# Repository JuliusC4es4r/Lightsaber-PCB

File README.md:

# Lightsaber-PCB
A lightsaber PCB for installing within lightsaber hilts. Designed to power and control neopixel LED strips and play sounds on a speaker. Charges its own battery via USB-C.

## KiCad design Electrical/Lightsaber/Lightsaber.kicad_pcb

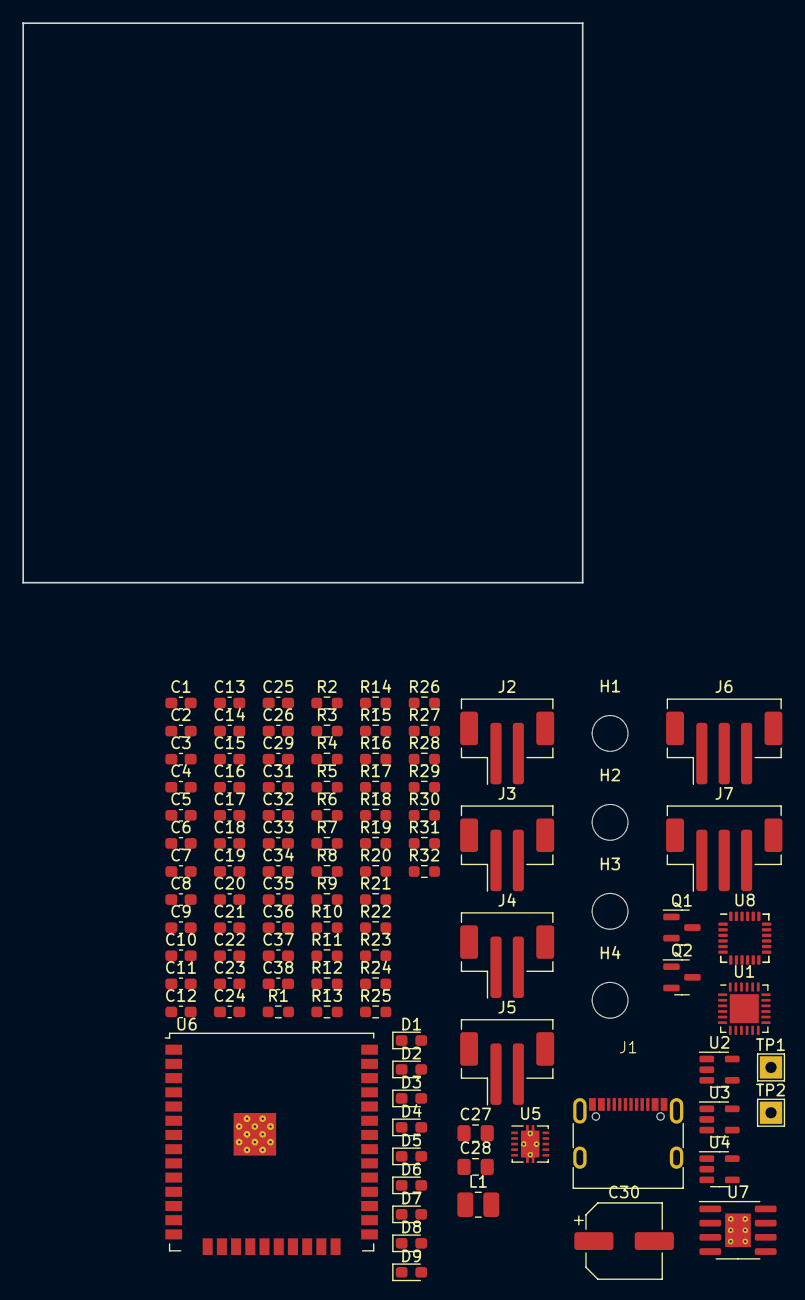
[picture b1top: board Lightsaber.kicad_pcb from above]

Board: 4 copper layers, 50.0 x 50.0 mm, 103 parts (0 on the bottom side), 58 nets, no tracks yet.

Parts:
C1, C3, C7, C8, C9, C12, C17, C32: 4u7; C_0603_1608Metric_Pad1.08x0.95mm_HandSolder
C2, C4, C10, C11, C16, C20, C29, C31, C33, C35, C37, C38: 100n; C_0603_1608Metric_Pad1.08x0.95mm_HandSolder
C5, C6, C13, C14, C15, C18, C19, C21, C22, C23, C24, C25, C26: 10uF; C_0603_1608Metric_Pad1.08x0.95mm_HandSolder
C27, C28: 10uF; C_0805_2012Metric_Pad1.18x1.45mm_HandSolder
C30: 100uF; CP_Elec_6.3x7.7
C34: 2.2n; C_0603_1608Metric_Pad1.08x0.95mm_HandSolder
C36: 10n; C_0603_1608Metric_Pad1.08x0.95mm_HandSolder
D1, D2, D4, D5: Blue; LED_0603_1608Metric_Pad1.05x0.95mm_HandSolder
D3, D6, D7, D8, D9: Green; LED_0603_1608Metric_Pad1.05x0.95mm_HandSolder
H1, H2, H3, H4: MountingHole; MountingHole_3.2mm_M3
J1: USB4105-GF-A; USB-C
J2, J3, J4, J5: B2B-PH-SM4-TB; JST_PH_B2B-PH-SM4-TB_1x02-1MP_P2.00mm_Vertical
J6, J7: B3B-PH-SM4-TB; JST_PH_B3B-PH-SM4-TB_1x03-1MP_P2.00mm_Vertical
L1: 2.2uH; L_1008_2520Metric_Pad1.43x2.20mm_HandSolder
Q1, Q2: BC817; SOT-23
R1, R11: 2kR; R_0603_1608Metric_Pad0.98x0.95mm_HandSolder
R2, R3: 5k1; R_0603_1608Metric_Pad0.98x0.95mm_HandSolder
R4, R5, R8, R9, R10, R12, R13, R16, R19, R25, R31, R32: 10kR; R_0603_1608Metric_Pad0.98x0.95mm_HandSolder
R6, R7, R21, R24, R26: 470R; R_0603_1608Metric_Pad0.98x0.95mm_HandSolder
R14: 100R; R_0603_1608Metric_Pad0.98x0.95mm_HandSolder
R15: 90.9kR; R_0603_1608Metric_Pad0.98x0.95mm_HandSolder
R17, R23: 0R; R_0603_1608Metric_Pad0.98x0.95mm_HandSolder
R18: 73.2kR; R_0603_1608Metric_Pad0.98x0.95mm_HandSolder
R20, R22, R28, R29, R30: 3.3k; R_0603_1608Metric_Pad0.98x0.95mm_HandSolder
R27: 10R; R_0603_1608Metric_Pad0.98x0.95mm_HandSolder
TP1, TP2: TestPoint; TestPoint_THTPad_2.0x2.0mm_Drill1.0mm
U1: CP2102N-Axx-xQFN24; QFN-24-1EP_4x4mm_P0.5mm_EP2.6x2.6mm
U2: MCP73831-2-OT; SOT-23-5
U3: AP2171W; SOT-23-5
U4: AP2161W; SOT-23-5
U5: TPS63000; Texas_DRC0010J_ThermalVias
U6: ESP32-WROOM-32U
U7: LM386; SOIC-8-1EP_3.9x4.9mm_P1.27mm_EP2.29x3mm_ThermalVias
U8: MPU-6050; InvenSense_QFN-24_4x4mm_P0.5mm

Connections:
+3V3: C3.1, C4.1, C17.1, C20.1, C21.1, C24.1, C33.1, C36.1, J3.1, J4.1, R1.1, R6.1, R7.1, R20.1, R22.1, R26.1, R31.1, R32.1, U1.5 (VIO), U1.6 (VDD), U6.2 (VDD), U8.8 (VLOGIC), U8.13 (VDD)
+5V: C7.1, C10.1, C13.1, C18.1, C19.1, C22.1, C23.1, C25.1, C26.1, C32.1, C35.1, J6.1, J7.1, R15.1, R30.1, U2.4 (V_{DD}), U3.1 (OUT), U5.1 (VOUT), U7.6 (V+)
+BATT: C5.1, C8.1, C12.1, J2.1, R11.1, U2.3 (V_{BAT}), U4.5 (IN)
/BOOT: C38.1, Q2.3 (C), R32.2, U6.25 (IO0)
/BTN_1: J3.2, R12.1, U6.26 (IO4)
/BTN_2: J4.2, R13.1, U6.29 (IO5)
/D+: J1.A6 (D+), J1.B6 (D+), U1.3 (D+)
/D-: J1.A7 (D-), J1.B7 (D-), U1.4 (D-)
/DAC: R17.1, R18.1, U6.10 (IO25)
/DOUT_1: J6.2, U6.27 (IO16)
/DOUT_2: J7.2, U6.28 (IO17)
/DTR: Q2.2 (E), R8.1, U1.23 (~DTR)
/EN: C37.1, Q1.3 (C), R31.2, U6.3 (EN)
/INT: U6.14 (IO12), U8.12 (INT)
/LED_1: R21.1, U6.30 (IO18)
/LED_2: R24.1, U6.31 (IO19)
/RST: R1.2, U1.9 (~RST)
/RTS: Q1.2 (E), R9.1, U1.19 (~RTS)
/RX: U1.20 (RXD), U6.35 (TXD0/IO1)
/SCL: R20.2, U6.36 (IO22), U8.23 (SCL)
/SDA: R22.2, U6.33 (IO21), U8.24 (SDA)
/SPKR_OUT: C30.2, J5.1
/TX: U1.21 (TXD), U6.34 (RXD0/IO3)
/VBUS_EN: R4.2, R5.1, U4.4 (~EN)
GND: C1.2, C2.2, C3.2, C4.2, C5.2, C6.2, C7.2, C8.2, C9.2, C10.2, C11.2, C12.2, C13.2, C14.2, C15.2, C16.2, C17.2, C18.2, C19.2, C20.2, C21.2, C22.2, C23.2, C24.2, C25.2, C26.2, C28.2, C31.2, C32.2, C33.2, C34.2, C35.2, C36.2, C37.2, C38.2, D4.1 (K), D5.1 (K), D6.1 (K), D7.1 (K), D8.1 (K), D9.1 (K), J1.13 (SHIELD), J1.14 (SHIELD), J1.15 (SHIELD), J1.16 (SHIELD), J1.A1 (GND), J1.A12 (GND), J2.2, J5.2, J6.3, J7.3, R2.2, R3.2, R5.2, R10.2, R12.2, R13.2, R16.2, R19.2, R27.1, U1.2 (GND), U1.25 (GND), U2.2 (V_{SS}), U3.2 (GND), U4.2 (GND), U5.3 (PGND), U5.9 (GND), U5.11 (PGND), U6.1 (GND), U6.15 (GND), U6.38 (GND), U6.39 (GND), U7.2 (-), U7.4 (GND), U8.1 (CLKIN), U8.9 (AD0), U8.11 (FSYNC), U8.18 (GND)
unnamed: C27.1, R23.1
unnamed: C27.2, U7.8 (GAIN)
unnamed: C28.1, R25.2
unnamed: C29.1, C30.1, TP2.1, U7.5
unnamed: C29.2, R27.2
unnamed: D1.2 (A), R6.2
unnamed: D1.1 (K), U1.14 (~TXT/GPIO.0)
unnamed: D2.2 (A), R7.2
unnamed: D2.1 (K), U1.13 (~RXT/GPIO.1)
unnamed: D3.2 (A), R11.2
unnamed: D3.1 (K), U2.1 (STAT)
unnamed: D4.2 (A), R21.2
unnamed: D5.2 (A), R24.2
unnamed: D6.2 (A), R26.2
unnamed: D7.2 (A), R28.2
unnamed: D8.2 (A), R29.2
unnamed: D9.2 (A), R30.2
unnamed: J1.A5 (CC1), R3.1
unnamed: J1.B5 (CC2), R2.1
unnamed: Q1.1 (B), R8.2
unnamed: Q2.1 (B), R9.2
unnamed: R23.2, U7.1 (GAIN)
unnamed: R10.1, U2.5 (PROG)
unnamed: C16.1, R14.2, U5.6 (EN), U5.7 (PS/SYNC), U5.8 (VINA)
unnamed: R15.2, R16.1, U5.10 (FB)
unnamed: L1.1, U5.4 (L1)
unnamed: L1.2, U5.2 (L2)
unnamed: R17.2, R18.2, R19.1, TP1.1, U7.3 (+)
unnamed: R25.1, U7.7 (BYPASS)
unnamed: C34.1, U8.20 (CPOUT)
unnamed: C31.1, U8.10 (REGOUT)
VBUS: C1.1, C2.1, C6.1, C9.1, J1.A4 (VBUS), J1.A9 (VBUS), R4.1, R29.1, U1.7 (VREGIN), U1.8 (VBUS), U3.4 (EN), U3.5 (IN)
V_BATT: C11.1, C14.1, C15.1, R14.1, R28.1, U4.1 (OUT), U5.5 (VIN)

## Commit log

2024-03-22 Porting over MK1.0 from Google drive
    also added mech and software folders
2024-03-22 made some testing code to test speaker
2024-03-25 Switched over to jst ph connectors
    wrote test code as well
